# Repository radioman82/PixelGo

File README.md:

# PixelGo – a Retro-Go fork for ESP boards

**PixelGo** is a retro-gaming firmware and development fork of Retro-Go, focused on ESP microcontrollers (especially the **ESP32-S3 DevKitC-1 N16R8** and Waveshare Nano-S3) with SPI TFT displays and custom handheld hardware.

* **Project:** PixelGo
* **Fork of:** [Retro-Go by ducalex](https://github.com/ducalex/retro-go)
* **Author / Maintainer:** `radioman82`
* **Development branch:** `nano-s3`
* **Releases:** [Download pre-built firmware images](https://github.com/radioman82/PixelGo/releases)

PixelGo incorporates hardware-specific adaptations, I2S sound architecture improvements, display timings, additional emulator ports and comprehensive documentation for the ESP32-S3 platform.

> 🎮 **Pre-built firmware images available:** Ready-to-flash binaries and full images for the ESP32-S3 can be downloaded directly from the [GitHub Releases](https://github.com/radioman82/PixelGo/releases) page.
>
> ⚠️ **Note on current release:** The emulators **Fake-08** (PICO-8) and **A500** (Amiga 500) as well as the games **Quake**, **Wolfenstein 3D**, and **Doom** are **not included** in the current pre-built release firmware.  
> *(Hinweis: Die Emulatoren Fake-08 und A500 sowie die Spiele Quake, Wolfenstein und Doom sind im aktuellen Release nicht enthalten.)*
>
> This is a development fork. Not all components described below are finished or fully integrated.

---

## 🤖 AI-Driven Hardware Co-Design & Digital Fabrication (PixelGo-01)

Ein zentrales **Alleinstellungsmerkmal** von PixelGo ist der vollständige, durchgängige Hardware-Entwicklungs- und Fertigungszyklus für das Handheld-Gehäuse und das Gamepad, der in direkter Pair-Programming-Zusammenarbeit mit der **Google DeepMind Antigravity KI** realisiert wurde:

* **Autonome parametrische CAD-Konstruktion in FreeCAD**:
  * Die Gehäuseteile (Frontschale, Rückschale, D-Pad, Aktions- und Menütasten sowie Löthilfen) wurden von der KI über Python-Skripte in **FreeCAD** konstruiert.
  * Sämtliche Innenmaße, Wandstärken, Toleranzen (PLA+ und TPU-Schrumpfung), M3-Einschmelzgewinde und passgenaue Aussparungen für das 2,8" ILI9341 TFT, den ESP32-S3, das TP4065-Lademodul, den MT3608 Step-Up, den MAX98357A I2S DAC, das MicroSD-Modul und den LiPo-Akku wurden millimetergenau aufeinander abgestimmt.
* **Direkte Steuerung des Artillery 3D-Druckers über USB-Schnittstelle**:
  * Die KI hat den Slicing-Prozess mit der CuraEngine vorbereitet und den **Artillery Sidewinder 3D-Drucker direkt über die serielle USB-Verbindung vom PC aus angesteuert**.
  * Die KI überwachte die Heizbett- und Düsentemperaturen in Echtzeit (`M105`, `M109`, `M190`), streamte den G-Code Zeile für Zeile und steuerte den physischen Druckvorgang der Gehäuseteile und Tasten vollständig autonom.
* **Maßgeschneidertes 1-lagiges KiCad 10 Gamepad-PCB**:
  * Für das Gehäuse entwarf die KI ein **100 % einlagiges Gamepad-PCB** (`B.Cu`), optimiert für das Selberätzen im **Tonertransfer-Verfahren (Bügelmethode)**.
  * Planare Leiterbahnführung **ohne jegliche Brücken oder Vias** (0 DRC-Fehler), flache Lötpads für Klingeldraht, integrierter 50 mm Prüfmaßstab und mikroskopische Zentrierpunkte für ein abrutschfreies Bohren der Tasterlöcher.

> 💡 **Hinweis zum Hardware-Aufbau (Prototyping / DIY-Hilfslösung):**  
> Die hier bereitgestellte einlagige Gamepad-Platine mit Einzelader-Verdrahtung (Klingeldraht) zu den einzelnen Modulen ist eine **pragmatische Hilfs- und Prototyplösung**, um das Handheld mit einfachen Maker-Mitteln zu Hause (Tonertransfer, Ätzbad, Standard-Breakout-Module) schnell und günstig realisieren zu können.  
> Für ein finales, kompaktes Gesamtsystem sind **professionell gefertigte Multi-Layer-Leiterplatten**, die sämtliche Elektronikkomponenten (ESP32-S3 SoC, Laderegelung, Step-Up-Wandler, I2S-Audio-DAC, MicroSD-Slot, Display-FPC-Stecker und Taster) monolithisch auf einem einzigen Board vereinen, natürlich **eindeutig im Vorteil** (minimale Bauhöhe, optimale EMV/Signalintegrität und Wegfall jeglichen Verdrahtungsaufwands).

📁 **CAD-Dateien, STLs & Druckanweisungen:** [`3ddruck/`](3ddruck/)  
📁 **KiCad-Projekt, Gerber- & Tonertransfer-Ätzvorlagen (PDF):** [`kicad/pixelgo_gamepad/`](kicad/pixelgo_gamepad/)

---

## Hardware

### ESP32-S3

Target board:

* ESP32-S3 DevKitC-1
* N16R8
* ESP32-S3
* 16 MB Flash
* 8 MB PSRAM

### ILI9341 SPI TFT

Current display configuration:

| Signal    |   GPIO / Connection |
| --------- | ------------------: |
| CS        | GND (fest auf Masse) |
| MOSI      |              GPIO12 |
| CLK       |              GPIO48 |
| DC        |              GPIO47 |
| RST       |               GPIO3 |
| Backlight |              GPIO39 |

* The **CS** (Chip Select) pin of the ILI9341 display is permanently tied to **GND** (configured as `GPIO_NUM_NC` in code).
* Touch functionality is **not used**.

### SD card / MicroSD Modul

The SD card is connected through SPI:

| Signal / Pin | ESP32-S3 / Level | Note |
| ------------ | ---------------: | ---- |
| MISO         |            GPIO9 | SPI Data Out / MISO |
| MOSI         |           GPIO11 | SPI Data In / MOSI |
| CLK          |           GPIO13 | SPI Clock / SCK |
| CS           |           GPIO10 | Chip Select |
| 3.3V (VCC)   |            3.3 V | Stromversorgung |
| GND          |              GND | Masse |

The SD card is used for ROMs, disk images and emulator data.

* **MicroSD-Modul als platzsparende Alternative:** Statt des integrierten Full-Size-SD-Kartenslots auf der Rückseite des TFT-Displays kann mit denselben SPI-Pins (GPIO9, GPIO11, GPIO13, GPIO10) auch ein separates **Micro-SD-Kartenmodul** verwendet werden. Dieses muss zusätzlich mit **3,3 V** und **GND** angeschlossen werden.
* **Gehäuse-Vorteil:** Durch den Verzicht auf die sperrige Standard-SD-Karte im TFT-Display bleibt deutlich mehr Platz im Gehäuse.

### Audio (MAX98357A I2S DAC)

I2S digital audio output configuration:

| Signal / Pin | ESP32-S3 / Level | Note |
| ------------ | ---------------: | ---- |
| BCLK (BCK)   |           GPIO41 | I2S Bit Clock |
| LRC (WS)     |           GPIO42 | Word Select / Left-Right Clock |
| DIN (DATA)   |           GPIO40 | Serial Data |
| SD           |            3.3 V | Festeingeschaltet (kein Enable-Pin im Code / `GPIO_NUM_NC`) |
| VIN          |      3.3 V / 5 V | Stromversorgung (5 V für 3 W an 4 Ω) |
| GND          |              GND | Masse |

---

## Input

The gamepad button configuration is:

| Function | Pad (W1) |   GPIO | Configuration | Physical Layout |
| -------- | :------: | -----: | ------------- | --------------- |
| DOWN     |  Pad 1   |  GPIO0 | Pull-up, Level 0 (Active Low) | Steuerkreuz Unten |
| LEFT     |  Pad 2   | GPIO45 | Pull-up, Level 0 (Active Low) | Steuerkreuz Links |
| UP       |  Pad 3   |  GPIO6 | Pull-up, Level 0 (Active Low) | Steuerkreuz Oben |
| RIGHT    |  Pad 4   |  GPIO7 | Pull-up, Level 0 (Active Low) | Steuerkreuz Rechts |
| SELECT   |  Pad 5   | GPIO16 | Pull-up, Level 0 (Active Low) | Menütaste Select |
| GND      |  Pad 6/7 |    GND | Gemeinsame Masse | Masse (Mittenanbindung) |
| START    |  Pad 8   | GPIO17 | Pull-up, Level 0 (Active Low) | Menütaste Start |
| MENU (Y) |  Pad 9   | GPIO18 | Pull-up, Level 0 (Active Low) | Aktionstaste Y / Menu |
| OPTION(X)|  Pad 10  |  GPIO8 | Pull-up, Level 0 (Active Low) | Aktionstaste X / Option |
| A        |  Pad 11  | GPIO15 | Pull-up, Level 0 (Active Low) | Aktionstaste A |
| B        |  Pad 12  |  GPIO5 | Pull-up, Level 0 (Active Low) | Aktionstaste B |

All buttons are configured with internal pull-ups (`pullup = 1`) and active-low trigger (`level = 0`) on the custom 1-layer PCB ([`kicad/pixelgo_gamepad/`](kicad/pixelgo_gamepad/)).

---

## Current Development Status

The ESP32-S3 port is actively being developed under the PixelGo project.

### Working / tested (included in release image)

* ESP32-S3 DevKitC-1 N16R8 & Waveshare Nano-S3 targets
* PixelGo builds successfully for ESP32-S3 with ESP-IDF
* ILI9341 & ST7789 SPI displays
* SD card support (SPI)
* ESP32-S3 input/button configuration
* emulator-specific input adaptations
* **Neo Geo Pocket / Neo Geo Pocket Color** core (RACE!) integrated and functional
* **WonderSwan / WonderSwan Color** core (Oswan) integrated and functional
* **MSX / MSX2** core (fMSX) integrated
* **retro-core** (NES, PC Engine, SMS, Game Gear, Atari Lynx), **gnuboy** (GB/GBC), **snes**, **gwenesis** (Mega Drive)
* Firmware images and app partitions generated with `rg_tool.py`

### Not Included in Current Pre-built Release

The following emulators and games are **not included** in the current pre-built release firmware:

* **Emulators:**
  * **Fake-08** (PICO-8) – experimental port under active development
  * **A500** (Amiga 500) – experimental proof-of-concept (see [a500/FAZIT.md](a500/FAZIT.md))
* **Games / Ports:**
  * **Quake** (`quake-go`)
  * **Wolfenstein 3D** (`wolf4sdl`)
  * **Doom** (`prboom-go`)

The current ESP32-S3 build system uses **ESP-IDF** rather than the Arduino build system used by some of the earlier experiments.

---

## Emulator Development

Several emulator components have been ported, adapted or integrated on the ESP32-S3.

### SNK Neo Geo Pocket & Neo Geo Pocket Color (RACE!)

* **App Target:** `ngp/`
* **Core Component:** `components/race/`
* **Supported File Types:** `.ngp`, `.ngc`, `.zip`
* **Partition Size:** 896 KB (`ngp` in `rg_tool.py`)
* **Key Implementation Details:**
  * Emulates the Toshiba TLCS-900H 16-bit CPU and Z80 sound co-processor.
  * Native 160×152 rendering scaled into Retro-Go display buffers.
  * **ESP32-S3 Audio Architecture:** Audio message buffers are strictly allocated in internal DRAM (`DRAM_ATTR audio_msg_t audio_pool[...]`) rather than PSRAM to guarantee jitter-free, glitch-free I2S DMA streaming without SPI bus contention.
  * **Universal S3 Sync Formula:** Includes dynamic sample rate compensation to prevent APB/I2S clock drift during CPU frequency adjustments and overclocking.
  * Dedicated FreeRTOS `audio_task` decoupled from the emulation loop via queues.

### Bandai WonderSwan & WonderSwan Color (Oswan)

* **App Target:** `oswan/`
* **Core Component:** `components/oswan/`
* **Supported File Types:** `.ws`, `.wsc`, `.zip`
* **Partition Size:** 640 KB (`oswan` in `rg_tool.py`)
* **Key Implementation Details:**
  * Emulates the NEC V30MZ CPU core (`nec.c`) and custom WonderSwan hardware.
  * Native 224×144 resolution with full monochrome and WonderSwan Color palette rendering (`WSRender.c`).
  * Dedicated input mapping (`ws_input_poll`) supporting X-Pad and Y-Pad button modes mapped seamlessly to standard Retro-Go gamepad controls.
  * WonderSwan Audio Processing Unit (APU) streaming audio directly into Retro-Go's DMA sound queue (`rg_audio_submit`).
  * Save states and EEPROM persistence support (`WSFileio.c`).

### Amiga 500 Development (UAE4all / FAME-C)

* **App Target:** `a500/`
* **Core Component:** `components/a500/`
* **Supported File Types:** `.adf`, `.zip`
* **Partition Size:** 2.0 MB (`a500` in `rg_tool.py`)
* **Status:** Integrated into Retro-Go as an **experimental** proof-of-concept (**not included in current pre-built release image**; see [a500/FAZIT.md](a500/FAZIT.md)).
  * Bootable into Kickstart 1.3 (`kick13.rom`), ADF floppy disk loading.
  * Paula 4-channel DMA audio over I2S and 320×240 RGB565 display output.
  * Gamepad joystick mode and selectable mouse mode via `SELECT`.
  * Detailed architectural findings and performance analysis (comparing Musashi vs. UAE4all/FAME-C, PSRAM latency bottlenecks, and frame rates) are documented in [a500/FAZIT.md](a500/FAZIT.md).

### PICO-8 Fantasy Console (Fake-08)

* **App Target:** `fake08/`
* **Core Component:** `fake-08/` (source tree adapted for ESP32-S3)
* **Supported File Types:** `.p8`, `.p8.png`
* **Status:** Integrated into the repository as an **experimental** proof-of-concept (sources ported, but **not included in current pre-built release build** `v1.04`; under active development).
* **Key Implementation Details:**
  * Uses the Fake-08 emulator engine (`vm.cpp`, `cart.cpp`, `z8lua`).
  * Custom Retro-Go Host integration in `fake08/main/main.cpp` using Retro-Go display buffers (`rg_surface_t`, `rg_display_submit`), audio DMA streaming (`rg_audio_submit`), and input polling.
  * Adapted for Xtensa / ESP-IDF C++ toolchain: fixed 32-bit fixed-point arithmetic (`fix32.h`), `luaconf.h` casting fixes, isolated LodePNG symbol conflicts, and routed console logging directly to standard output.
  * ROMs and cartridges are located at `/sd/roms/pico8`.

### Standalone Game Ports (Quake, Wolfenstein 3D, Doom)

* **App Targets:** `quake-go/` (Quake), `wolf4sdl/` (Wolfenstein 3D), `prboom-go/` (Doom)
* **Status:** Port sources exist in the repository, but are **not included in the current pre-built release firmware**.
  * These ports can be compiled individually or integrated into custom partition layouts if flash space permits.

---

## Documentation

Additional development documentation is included in:

* `Retro go mit esp32s3 R16N8.docx`: Records early hardware tests and configurations.
* [a500/FAZIT.md](a500/FAZIT.md): Comprehensive evaluation of the Amiga 500 port on ESP32-S3.

---

## Build

The ESP32-S3 targets are built using `rg_tool.py` on top of the ESP-IDF environment.

To build specific emulator binaries:

```bash
# Build Neo Geo Pocket
python rg_tool.py --target esp32-s3-devkit build ngp

# Build WonderSwan
python rg_tool.py --target esp32-s3-devkit build oswan

# Build Fake-08 (PICO-8, experimental)
python rg_tool.py --target esp32-s3-devkit build fake08

# Build all configured applications
python rg_tool.py --target esp32-s3-devkit build
```

Successful builds generate the binaries in each app's `build` directory:

```text
ngp/build/ngp.bin
oswan/build/oswan.bin
fake08/build/fake08.bin
launcher/build/launcher.bin
```

---

## Development Notes

PixelGo is primarily an active development project and evolving retro-gaming platform for ESP boards.

Hardware configuration and emulator support may change as development continues.

The goal is to maintain a high-performance, well-documented ESP32-S3 retro platform while expanding emulator support, audio fidelity, and hardware-specific improvements.

---

## Credits & Upstream Project

PixelGo is based on the fantastic upstream project [Retro-Go by ducalex](https://github.com/ducalex/retro-go).

* **Upstream Repository:** [https://github.com/ducalex/retro-go](https://github.com/ducalex/retro-go)
* **Original Author:** ducalex and contributors
* **Artwork Pack:** [retro-go-covers](https://github.com/ducalex/retro-go-covers)

Please refer to the original repository for upstream documentation and legacy platform support (ODROID-GO, MRGC-G32).

---

## License

Everything in this project is licensed under the [GPLv2 license](COPYING) with the exception of specific emulator cores:
* `fmsx/components/fmsx`: MSX emulator (custom non-commercial license)
* `retro-core/components/handy`: Lynx emulator (zlib)
* `fake-08`: PICO-8 emulator by jtothebell (MIT)

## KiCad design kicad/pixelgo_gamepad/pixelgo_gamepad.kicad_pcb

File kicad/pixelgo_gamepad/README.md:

# PixelGo-01 Gamepad PCB (KiCad 10)

Einlagiges Gamepad-Platinenlayout (Single-Sided / `B.Cu` only) für den **PixelGo-01** Handheld (ESP32-S3 DevKitC-1 N16R8).

> 💡 **Hinweis zum Hardware-Ansatz (DIY-Hilfslösung vs. professionelle Leiterplatte):**  
> Die hier bereitgestellte einlagige Gamepad-Platine mit Einzelader-Verdrahtung (Klingeldraht) zu den einzelnen Modulen ist eine **pragmatische Hilfs- und Prototyplösung**, um das Projekt mit einfachen Maker-Mitteln zu Hause (Tonertransfer mit dem Bügeleisen, Ätzbad, Standard-Breakout-Module) schnell und kostengünstig zu realisieren.  
> Für eine finale Serienreife oder maximale Kompaktheit sind **professionell gefertigte Multi-Layer-Leiterplatten**, die sämtliche Komponenten (ESP32-S3 SoC, Laderegler, Step-Up-Wandler, I2S-DAC, MicroSD-Slot, Display-FPC und Taster) monolithisch auf einer einzigen Platine vereinen, natürlich **eindeutig im Vorteil** (flachere Bauhöhe, perfekte EMV/Signalintegrität und kein manueller Verdrahtungsaufwand).

---

## 3D-Vorschau

| Oberseite (Bestückungsseite) | Unterseite (Lötseite B.Cu) |
| :---: | :---: |
|  |  |

---

## Technische Daten

* **Abmessungen:** $91.0 \times 70.0\text{ mm}$ (Ecken gerundet $R = 2.0\text{ mm}$)
* **Kupferlagen:** 1 Lage (`B.Cu` Unterseite) – 0 Kupfer auf `F.Cu`, keine Durchkontaktierungen/Vias, keine Drahtbrücken
* **Befestigung:** 4x M3-Bohrungen ($\varnothing 3.2\text{ mm}$) im Raster $83.5 \times 61.0\text{ mm}$
* **Bedienelemente:** 10x Standard-Mikrotaster 6x6 mm THT (`SW_PUSH_6mm`)
* **Anschluss:** 12 durchkontaktierte Lötpads `W1` ($\varnothing 1.1\text{ mm}$ Bohrung, $\varnothing 2.2\text{ mm}$ Pad, 2.54 mm Raster)
* **Design Rules (DRC):** 0 Fehler, 0 Warnungen, 0 unverbundene Netze

---

## Pinbelegung Drahtanschluss (`W1`)

| Pad | Signal | ESP32-S3 | Funktion |
| :---: | :--- | :---: | :--- |
| **1** | `BTN_DOWN` | **GPIO 0** | D-Pad Unten |
| **2** | `BTN_LEFT` | **GPIO 45** | D-Pad Links |
| **3** | `BTN_UP` | **GPIO 6** | D-Pad Oben |
| **4** | `BTN_RIGHT` | **GPIO 7** | D-Pad Rechts |
| **5** | `BTN_SELECT` | **GPIO 16** | Select |
| **6** | `GND` | **GND** | Masse 1 |
| **7** | `GND` | **GND** | Masse 2 |
| **8** | `BTN_START` | **GPIO 17** | Start |
| **9** | `BTN_Y` | **GPIO 18** | Action Y / Menu |
| **10** | `BTN_X` | **GPIO 8** | Action X / Option |
| **11** | `BTN_A` | **GPIO 15** | Action A |
| **12** | `BTN_B` | **GPIO 5** | Action B |

---

## Tonertransfer-Druckvorlagen (Bügelmethode)

* **[pixelgo_gamepad_tonertransfer_B_Cu.pdf](pixelgo_gamepad_tonertransfer_B_Cu.pdf)** *(Standard für Tonertransfer / Bügeleisen)*
  * Maßstab 1:1 (DIN A4), tiefschwarz, mit 50.0 mm Prüfbalken, Schnittmarken und mikroskopischen Zentrierkörnerpunkten für die Bohrungen.
* **[pixelgo_gamepad_tonertransfer_B_Cu_mirrored.pdf](pixelgo_gamepad_tonertransfer_B_Cu_mirrored.pdf)** *(Gespiegelt für Fotopositiv-Belichtung)*
* **[pixelgo_gamepad_tonertransfer_B_Cu.svg](pixelgo_gamepad_tonertransfer_B_Cu.svg)** *(Vektorgrafik)*

---

## Dateien im Ordner

* `pixelgo_gamepad.kicad_pcb`: KiCad 10 Platinenlayout
* `pixelgo_gamepad.kicad_sch`: KiCad 10 Schaltplan
* `pixelgo_gamepad.kicad_pro`: KiCad 10 Projektdatei
* `build_pixelgo_pcb.py`: Python-Skript zur automatisierten Neugenerierung
* `gerbers/`: Vollständiger Fertigungssatz (Gerber RS-274X & Excellon-Bohrdaten)

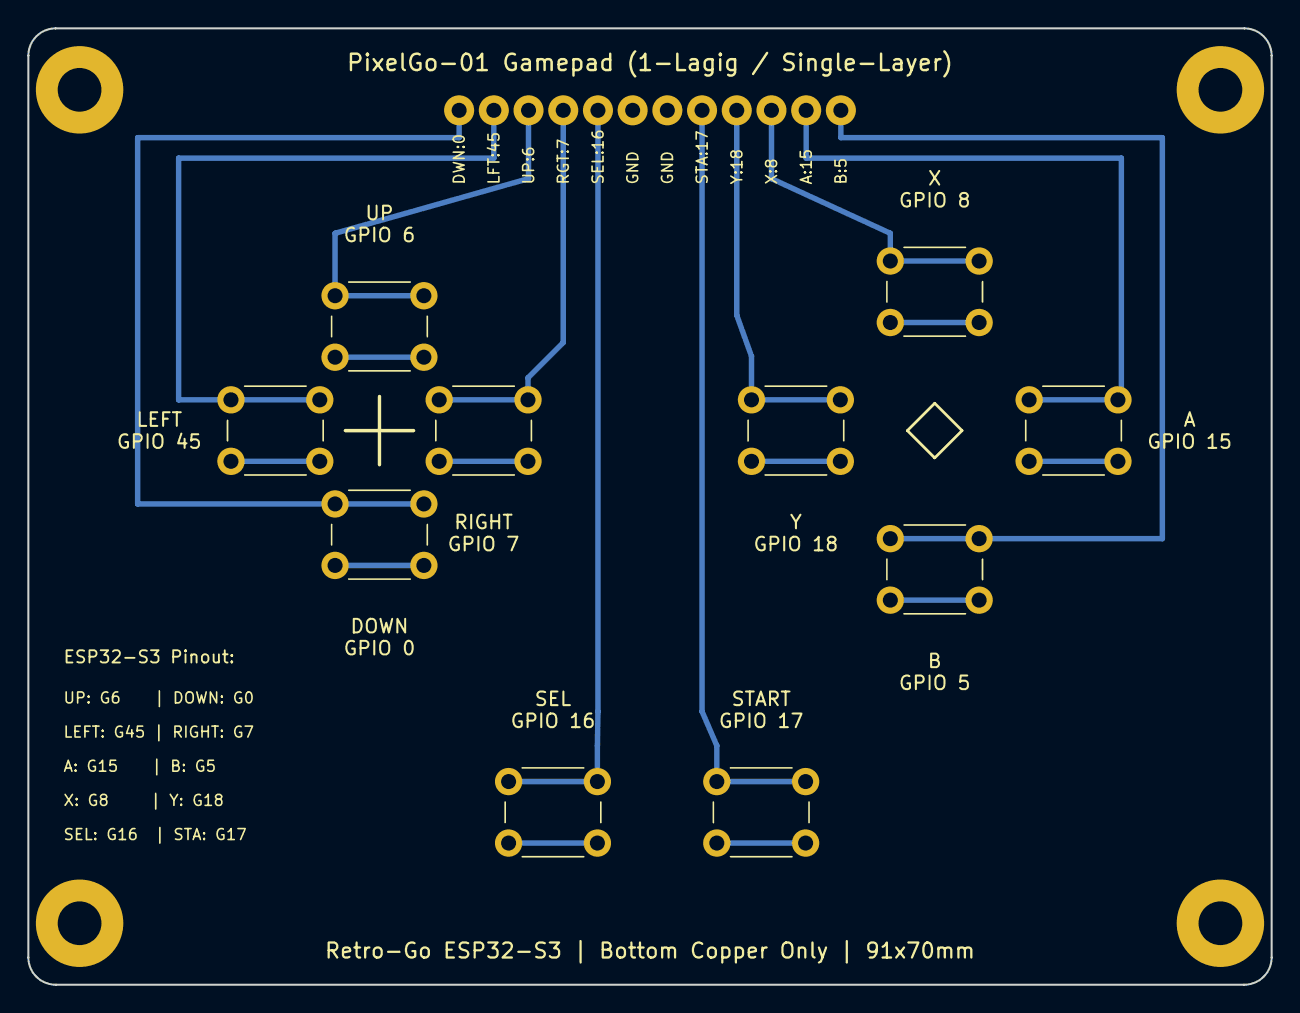
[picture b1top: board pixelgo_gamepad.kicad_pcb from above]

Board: 2 copper layers, 91.0 x 70.0 mm, 15 parts (0 on the bottom side), 11 nets.

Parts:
H1, H2, H3, H4: MountingHole_3.2mm_M3_Pad
SW1: UP; SW_PUSH_6mm
SW2: DOWN; SW_PUSH_6mm
SW3: LEFT; SW_PUSH_6mm
SW4: RIGHT; SW_PUSH_6mm
SW5: A; SW_PUSH_6mm
SW6: B; SW_PUSH_6mm
SW7: X; SW_PUSH_6mm
SW8: Y; SW_PUSH_6mm
SW9: SEL; SW_PUSH_6mm
SW10: START; SW_PUSH_6mm
W1: Klingeldraht-Pads

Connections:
BTN_A: SW5.1, W1.11
BTN_B: SW6.1, W1.12
BTN_DOWN: SW2.1, W1.1
BTN_LEFT: SW3.1, W1.2
BTN_RIGHT: SW4.1, W1.4
BTN_SELECT: SW9.1, W1.5
BTN_START: SW10.1, W1.8
BTN_UP: SW1.1, W1.3
BTN_X: SW7.1, W1.10
BTN_Y: SW8.1, W1.9
GND: H1.1, H2.1, H3.1, H4.1, SW1.2, SW2.2, SW3.2, SW4.2, SW5.2, SW6.2, SW7.2, SW8.2, SW9.2, SW10.2, W1.6, W1.7

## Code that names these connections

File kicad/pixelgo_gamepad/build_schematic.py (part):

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        sch_text += f"\t(label \"{net_name}\" (at 40.64 {py} 180) (fields_autoplaced yes) (effects (font (size 1.27 1.27))) (uuid \"{gen_uuid()}\"))\n"

switches = [
    ("SW3",  "BTN_LEFT",   "LEFT (GPIO 45)",  120.0,  50.0),
    ("SW1",  "BTN_UP",     "UP (GPIO 6)",     120.0,  65.0),
    ("SW2",  "BTN_DOWN",   "DOWN (GPIO 0)",   120.0,  80.0),
    ("SW4",  "BTN_RIGHT",  "RIGHT (GPIO 7)",  120.0,  95.0),
    ("SW9",  "BTN_SELECT", "SELECT (GPIO 16)",120.0, 110.0),
    ("SW10", "BTN_START",  "START (GPIO 17)", 120.0, 125.0),
    ("SW8",  "BTN_Y",      "Y (GPIO 18)",     120.0, 140.0),
    ("SW6",  "BTN_B",      "B (GPIO 5)",      120.0, 155.0),
    ("SW7",  "BTN_X",      "X (GPIO 8)",      120.0, 170.0),
    ("SW5",  "BTN_A",      "A (GPIO 15)",     120.0, 185.0),
]

for ref, net_name, val_label, sx, sy in switches:
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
